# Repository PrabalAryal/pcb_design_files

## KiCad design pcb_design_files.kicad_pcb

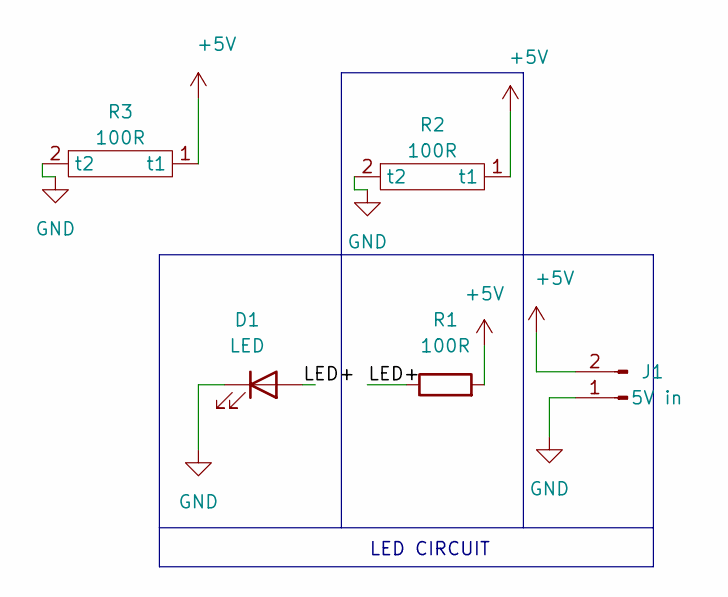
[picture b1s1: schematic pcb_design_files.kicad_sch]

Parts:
D1: LED; LED_D5.0mm_Horizontal_O1.27mm_Z15.0mm
J1: 5V in; PinSocket_1x02_P2.54mm_Vertical
R1: 100R; R_Axial_DIN0207_L6.3mm_D2.5mm_P2.54mm_Vertical
R2: 100R; unique_res
R3: 100R; ress_smd

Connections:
+5V: J1.2, R1.2, R2.1 (t1), R3.1 (t1)
/LED+: D1.2 (A), R1.1
GND: D1.1 (K), J1.1, R2.2 (t2), R3.2 (t2)

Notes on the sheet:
LED CIRCUIT

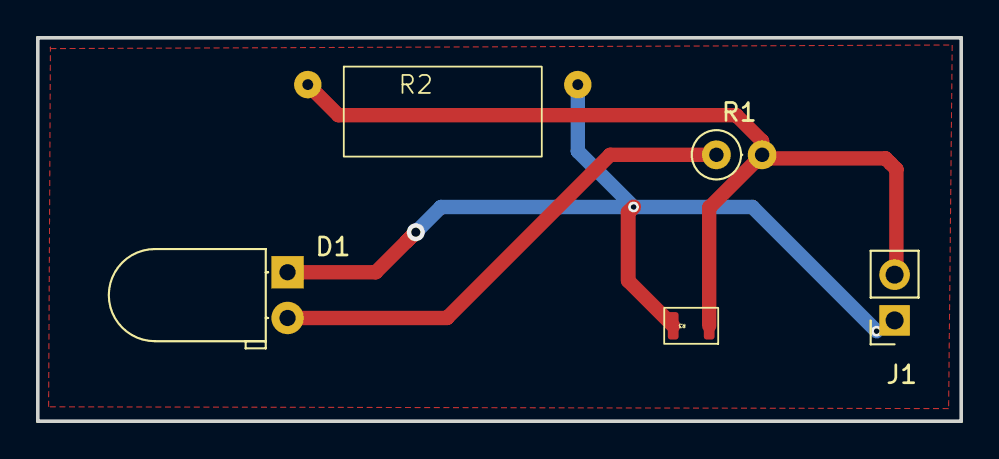
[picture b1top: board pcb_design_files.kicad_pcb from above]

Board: 2 copper layers, 51.3 x 21.3 mm, 5 parts (0 on the bottom side), 3 nets.

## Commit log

2024-07-20 1st day training
